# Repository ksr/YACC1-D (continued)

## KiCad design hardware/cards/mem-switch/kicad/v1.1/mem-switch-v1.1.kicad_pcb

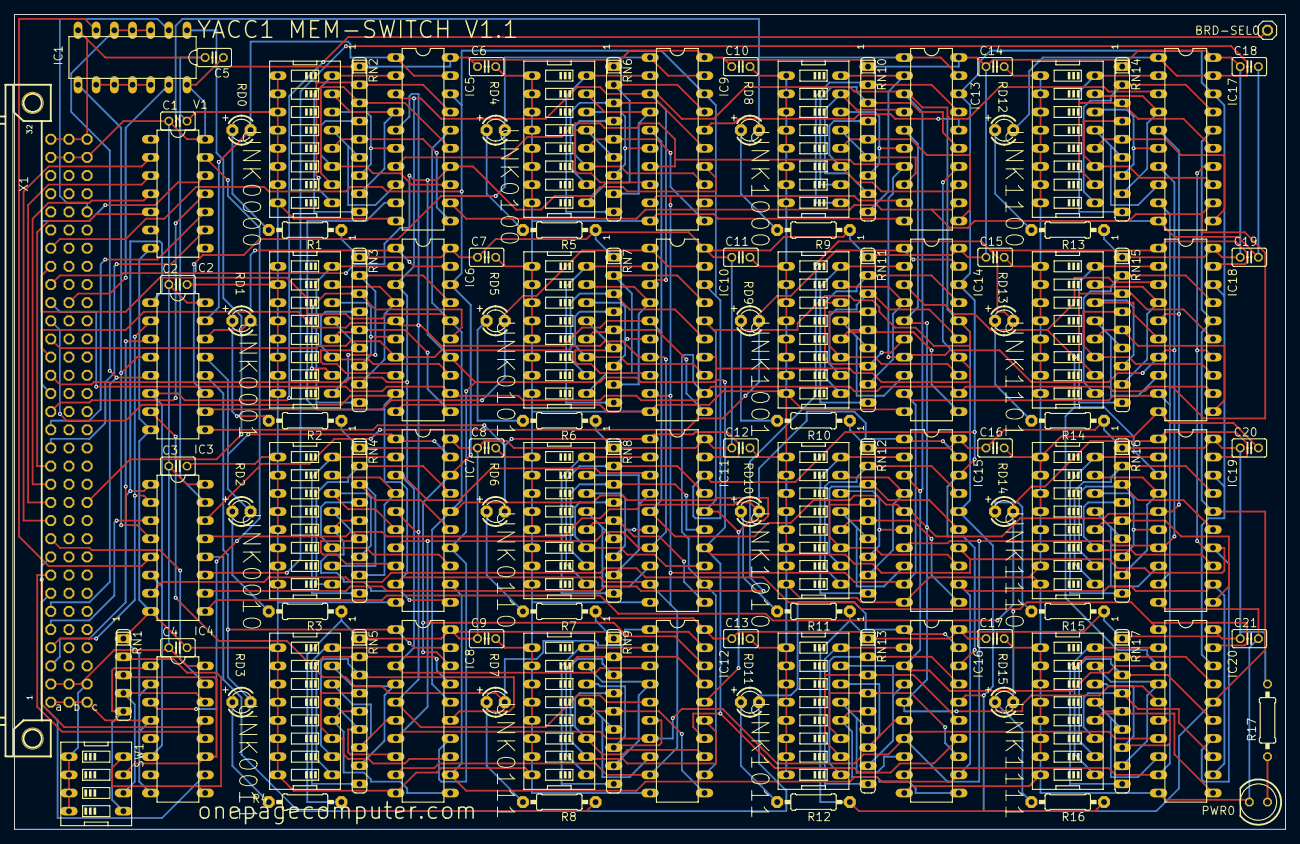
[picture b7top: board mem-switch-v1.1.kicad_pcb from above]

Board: 2 copper layers, 177.8 x 114.0 mm, 112 parts (0 on the bottom side), 199 nets.

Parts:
BRD-SEL0: PINHD-1X1; 1X01
C1, C2, C3, C4, C5, C6, C7, C8, C9, C10, C11, C12, C13, C14, C15, C16, C17, C18, C19, C20, C21: C025-025X050
IC1: 74ALS27N; DIL14
IC2, IC3: 74LS138N; DIL16
IC4: 74LS85N; DIL16
IC5, IC6, IC7, IC8, IC9, IC10, IC11, IC12, IC13, IC14, IC15, IC16, IC17, IC18, IC19, IC20: 74LS244N; DIL20
PWR0: LED5MM
R1, R2, R3, R4, R5, R6, R7, R8, R9, R10, R11, R12, R13, R14, R15, R16: 0207_10
R17: 330; 0207_10
RD0, RD1, RD2, RD3, RD4, RD5, RD6, RD7, RD8, RD9, RD10, RD11, RD12, RD13, RD14, RD15: LED3MM
RN1: SIL5
RN2, RN3, RN4, RN5, RN6, RN7, RN8, RN9, RN10, RN11, RN12, RN13, RN14, RN15, RN16, RN17: SIL9
SW1: EDG-04
UNK0000, UNK0001, UNK0010, UNK0011, UNK0100, UNK0101, UNK0110, UNK0111, UNK1000, UNK1001, UNK1010, UNK1011, UNK1100, UNK1101, UNK1110, UNK1111: EDG-08
V1: 744078N; DIL14
X1: FABC96R

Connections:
-BUS-EN: IC1.2, X1.C28
-MEM-RD: IC1.13, X1.B23
-VMA: IC1.1, X1.C12
ADDR0: IC2.1, IC3.1, X1.A3
ADDR1: IC2.2, IC3.2, X1.A4
ADDR2: IC2.3, IC3.3, X1.A5
ADDR3: IC1.3, IC1.4, IC1.5, IC2.5, X1.A6
ADDR4: IC4.10, X1.A7
ADDR5: IC4.12, X1.A8
ADDR6: IC4.13, X1.A9
ADDR7: IC4.15, X1.A10
ADDR8: V1.2, X1.A11
ADDR9: V1.3, X1.A12
ADDR10: V1.4, X1.A13
ADDR11: V1.5, X1.A14
ADDR12: V1.9, X1.A15
ADDR13: V1.10, X1.A16
ADDR14: V1.11, X1.A17
ADDR15: V1.12, X1.A18
DATA0: IC5.3, IC6.3, IC7.3, IC8.3, IC9.3, IC10.3, IC11.3, IC12.3, IC13.3, IC14.3, IC15.3, IC16.3, IC17.3, IC18.3, IC19.3, IC20.3, X1.A19
DATA1: IC5.5, IC6.5, IC7.5, IC8.5, IC9.5, IC10.5, IC11.5, IC12.5, IC13.5, IC14.5, IC15.5, IC16.5, IC17.5, IC18.5, IC19.5, IC20.5, X1.A20
DATA2: IC5.7, IC6.7, IC7.7, IC8.7, IC9.7, IC10.7, IC11.7, IC12.7, IC13.7, IC14.7, IC15.7, IC16.7, IC17.7, IC18.7, IC19.7, IC20.7, X1.A21
DATA3: IC5.9, IC6.9, IC7.9, IC8.9, IC9.9, IC10.9, IC11.9, IC12.9, IC13.9, IC14.9, IC15.9, IC16.9, IC17.9, IC18.9, IC19.9, IC20.9, X1.A22
DATA4: IC5.12, IC6.12, IC7.12, IC8.12, IC9.12, IC10.12, IC11.12, IC12.12, IC13.12, IC14.12, IC15.12, IC16.12, IC17.12, IC18.12, IC19.12, IC20.12, X1.A23
DATA5: IC5.14, IC6.14, IC7.14, IC8.14, IC9.14, IC10.14, IC11.14, IC12.14, IC13.14, IC14.14, IC15.14, IC16.14, IC17.14, IC18.14, IC19.14, IC20.14, X1.A24
DATA6: IC5.16, IC6.16, IC7.16, IC8.16, IC9.16, IC10.16, IC11.16, IC12.16, IC13.16, IC14.16, IC15.16, IC16.16, IC17.16, IC18.16, IC19.16, IC20.16, X1.A25
DATA7: IC5.18, IC6.18, IC7.18, IC8.18, IC9.18, IC10.18, IC11.18, IC12.18, IC13.18, IC14.18, IC15.18, IC16.18, IC17.18, IC18.18, IC19.18, IC20.18, X1.A26
GND: C1.2, C2.2, C3.2, C4.2, C5.2, C6.2, C7.2, C8.2, C9.2, C10.2, C11.2, C12.2, C13.2, C14.2, C15.2, C16.2, C17.2, C18.2, C19.2, C20.2, C21.2, IC1.7, IC2.8, IC3.8, IC4.2, IC4.4, IC4.8, IC5.10, IC6.10, IC7.10, IC8.10, IC9.10, IC10.10, IC11.10, IC12.10, IC13.10, IC14.10, IC15.10, IC16.10, IC17.10, IC18.10, IC19.10, IC20.10, PWR0.K, RN1.1, UNK0000.9, UNK0000.10, UNK0000.11, UNK0000.12, UNK0000.13, UNK0000.14, UNK0000.15, UNK0000.16, UNK0001.9, UNK0001.10, UNK0001.11, UNK0001.12, UNK0001.13, UNK0001.14, UNK0001.15, UNK0001.16, UNK0010.9, UNK0010.10, UNK0010.11, UNK0010.12, UNK0010.13, UNK0010.14, UNK0010.15, UNK0010.16, UNK0011.9, UNK0011.10, UNK0011.11, UNK0011.12, UNK0011.13, UNK0011.14, UNK0011.15, UNK0011.16, UNK0100.9, UNK0100.10, UNK0100.11, UNK0100.12, UNK0100.13, UNK0100.14, UNK0100.15, UNK0100.16, UNK0101.9, UNK0101.10, UNK0101.11, UNK0101.12, UNK0101.13, UNK0101.14, UNK0101.15, UNK0101.16, UNK0110.9, UNK0110.10, UNK0110.11, UNK0110.12, UNK0110.13, UNK0110.14, UNK0110.15, UNK0110.16, UNK0111.9, UNK0111.10, UNK0111.11, UNK0111.12, UNK0111.13, UNK0111.14, UNK0111.15, UNK0111.16, UNK1000.9, UNK1000.10, UNK1000.11, UNK1000.12, UNK1000.13, UNK1000.14, UNK1000.15, UNK1000.16, UNK1001.9, UNK1001.10, UNK1001.11, UNK1001.12, UNK1001.13, UNK1001.14, UNK1001.15, UNK1001.16, UNK1010.9, UNK1010.10, UNK1010.11, UNK1010.12, UNK1010.13, UNK1010.14, UNK1010.15, UNK1010.16, UNK1011.9, UNK1011.10, UNK1011.11, UNK1011.12, UNK1011.13, UNK1011.14, UNK1011.15, UNK1011.16, UNK1100.9, UNK1100.10, UNK1100.11, UNK1100.12, UNK1100.13, UNK1100.14, UNK1100.15, UNK1100.16, UNK1101.9, UNK1101.10, UNK1101.11, UNK1101.12, UNK1101.13, UNK1101.14, UNK1101.15, UNK1101.16, UNK1110.9, UNK1110.10, UNK1110.11, UNK1110.12, UNK1110.13, UNK1110.14, UNK1110.15, UNK1110.16, UNK1111.9, UNK1111.10, UNK1111.11, UNK1111.12, UNK1111.13, UNK1111.14, UNK1111.15, UNK1111.16, V1.7, X1.A1, X1.A32, X1.B1, X1.B32, X1.C1, X1.C32
unnamed: IC5.17, RN2.2, UNK0000.1
unnamed: IC5.15, RN2.3, UNK0000.2
unnamed: IC5.13, RN2.4, UNK0000.3
unnamed: IC5.11, RN2.5, UNK0000.4
unnamed: IC5.8, RN2.6, UNK0000.5
unnamed: BRD-SEL0.1, IC2.6, IC3.6, IC4.6
unnamed: IC5.6, RN2.7, UNK0000.6
unnamed: IC5.4, RN2.8, UNK0000.7
unnamed: IC5.2, RN2.9, UNK0000.8
unnamed: IC6.17, RN3.2, UNK0001.1
unnamed: PWR0.A, R17.1
unnamed: IC6.15, RN3.3, UNK0001.2
unnamed: IC6.13, RN3.4, UNK0001.3
unnamed: IC6.11, RN3.5, UNK0001.4
unnamed: IC6.8, RN3.6, UNK0001.5
unnamed: IC6.6, RN3.7, UNK0001.6
unnamed: IC6.4, RN3.8, UNK0001.7
unnamed: IC6.2, RN3.9, UNK0001.8
unnamed: IC1.9, IC1.10, IC1.11, IC1.12
unnamed: IC7.17, RN4.2, UNK0010.1
unnamed: IC7.15, RN4.3, UNK0010.2
unnamed: IC7.13, RN4.4, UNK0010.3
unnamed: IC7.11, RN4.5, UNK0010.4
unnamed: IC7.8, RN4.6, UNK0010.5
unnamed: IC7.6, RN4.7, UNK0010.6
unnamed: IC7.4, RN4.8, UNK0010.7
unnamed: IC7.2, RN4.9, UNK0010.8
unnamed: IC4.9, RN1.2, SW1.8
unnamed: IC8.17, RN5.2, UNK0011.1
unnamed: IC8.15, RN5.3, UNK0011.2
unnamed: IC8.13, RN5.4, UNK0011.3
unnamed: IC8.11, RN5.5, UNK0011.4
unnamed: IC8.8, RN5.6, UNK0011.5
unnamed: IC8.6, RN5.7, UNK0011.6
unnamed: IC8.4, RN5.8, UNK0011.7
unnamed: IC8.2, RN5.9, UNK0011.8
unnamed: IC1.6, IC3.5
unnamed: IC9.17, RN6.2, UNK0100.1
unnamed: IC9.15, RN6.3, UNK0100.2
unnamed: IC9.13, RN6.4, UNK0100.3
unnamed: IC9.11, RN6.5, UNK0100.4
unnamed: IC9.8, RN6.6, UNK0100.5
unnamed: IC9.6, RN6.7, UNK0100.6
unnamed: IC9.4, RN6.8, UNK0100.7
unnamed: IC9.2, RN6.9, UNK0100.8
unnamed: IC4.11, RN1.3, SW1.7
unnamed: IC10.17, RN7.2, UNK0101.1
unnamed: IC10.15, RN7.3, UNK0101.2
unnamed: IC10.13, RN7.4, UNK0101.3
unnamed: IC10.11, RN7.5, UNK0101.4
unnamed: IC10.8, RN7.6, UNK0101.5
unnamed: IC10.6, RN7.7, UNK0101.6
unnamed: IC10.4, RN7.8, UNK0101.7
unnamed: IC10.2, RN7.9, UNK0101.8
unnamed: IC4.3, V1.13
unnamed: IC11.17, RN8.2, UNK0110.1
unnamed: IC11.15, RN8.3, UNK0110.2
unnamed: IC11.13, RN8.4, UNK0110.3
unnamed: IC11.11, RN8.5, UNK0110.4
unnamed: IC11.8, RN8.6, UNK0110.5
unnamed: IC11.6, RN8.7, UNK0110.6
unnamed: IC11.4, RN8.8, UNK0110.7
unnamed: IC11.2, RN8.9, UNK0110.8
unnamed: IC4.14, RN1.4, SW1.6
unnamed: IC12.17, RN9.2, UNK0111.1
unnamed: IC12.15, RN9.3, UNK0111.2
unnamed: IC12.13, RN9.4, UNK0111.3
unnamed: IC12.11, RN9.5, UNK0111.4
unnamed: IC12.8, RN9.6, UNK0111.5
unnamed: IC12.6, RN9.7, UNK0111.6
unnamed: IC12.4, RN9.8, UNK0111.7
unnamed: IC12.2, RN9.9, UNK0111.8
unnamed: IC4.1, RN1.5, SW1.5
unnamed: IC13.17, RN10.2, UNK1000.1
unnamed: IC13.15, RN10.3, UNK1000.2
unnamed: IC13.13, RN10.4, UNK1000.3
unnamed: IC13.11, RN10.5, UNK1000.4
unnamed: IC13.8, RN10.6, UNK1000.5
unnamed: IC13.6, RN10.7, UNK1000.6
unnamed: IC13.4, RN10.8, UNK1000.7
unnamed: IC13.2, RN10.9, UNK1000.8
unnamed: IC1.8, IC2.4, IC3.4
unnamed: IC14.17, RN11.2, UNK1001.1
unnamed: IC14.15, RN11.3, UNK1001.2
unnamed: IC14.13, RN11.4, UNK1001.3
unnamed: IC14.11, RN11.5, UNK1001.4
unnamed: IC14.8, RN11.6, UNK1001.5
unnamed: IC14.6, RN11.7, UNK1001.6
unnamed: IC14.4, RN11.8, UNK1001.7
unnamed: IC14.2, RN11.9, UNK1001.8
unnamed: R1.2, RD0.A
unnamed: IC15.17, RN12.2, UNK1010.1
unnamed: IC15.15, RN12.3, UNK1010.2
unnamed: IC15.13, RN12.4, UNK1010.3
unnamed: IC15.11, RN12.5, UNK1010.4
unnamed: IC15.8, RN12.6, UNK1010.5
unnamed: IC15.6, RN12.7, UNK1010.6
unnamed: IC15.4, RN12.8, UNK1010.7
unnamed: IC15.2, RN12.9, UNK1010.8
unnamed: R2.2, RD1.A
unnamed: IC16.17, RN13.2, UNK1011.1
unnamed: IC16.15, RN13.3, UNK1011.2
unnamed: IC16.13, RN13.4, UNK1011.3
unnamed: IC16.11, RN13.5, UNK1011.4
unnamed: IC16.8, RN13.6, UNK1011.5
unnamed: IC16.6, RN13.7, UNK1011.6
unnamed: IC16.4, RN13.8, UNK1011.7
unnamed: IC16.2, RN13.9, UNK1011.8
unnamed: R3.2, RD2.A
unnamed: IC17.17, RN14.2, UNK1100.1
unnamed: IC17.15, RN14.3, UNK1100.2
unnamed: IC17.13, RN14.4, UNK1100.3
unnamed: IC17.11, RN14.5, UNK1100.4
unnamed: IC17.8, RN14.6, UNK1100.5
unnamed: IC17.6, RN14.7, UNK1100.6
unnamed: IC17.4, RN14.8, UNK1100.7
unnamed: IC17.2, RN14.9, UNK1100.8
unnamed: R4.2, RD3.A
unnamed: IC18.17, RN15.2, UNK1101.1
unnamed: IC18.15, RN15.3, UNK1101.2
unnamed: IC18.13, RN15.4, UNK1101.3
unnamed: IC18.11, RN15.5, UNK1101.4
unnamed: IC18.8, RN15.6, UNK1101.5
unnamed: IC18.6, RN15.7, UNK1101.6
unnamed: IC18.4, RN15.8, UNK1101.7
unnamed: IC18.2, RN15.9, UNK1101.8
unnamed: R5.2, RD4.A
unnamed: IC19.17, RN16.2, UNK1110.1
unnamed: IC19.15, RN16.3, UNK1110.2
unnamed: IC19.13, RN16.4, UNK1110.3
unnamed: IC19.11, RN16.5, UNK1110.4
unnamed: IC19.8, RN16.6, UNK1110.5
unnamed: IC19.6, RN16.7, UNK1110.6
unnamed: IC19.4, RN16.8, UNK1110.7
unnamed: IC19.2, RN16.9, UNK1110.8
unnamed: R6.2, RD5.A
unnamed: IC20.17, RN17.2, UNK1111.1
unnamed: IC20.15, RN17.3, UNK1111.2
unnamed: IC20.13, RN17.4, UNK1111.3
unnamed: IC20.11, RN17.5, UNK1111.4
unnamed: IC20.8, RN17.6, UNK1111.5
unnamed: IC20.6, RN17.7, UNK1111.6
unnamed: IC20.4, RN17.8, UNK1111.7
unnamed: IC20.2, RN17.9, UNK1111.8
unnamed: R7.2, RD6.A
unnamed: R8.2, RD7.A
unnamed: R9.2, RD8.A
unnamed: R10.2, RD9.A
unnamed: R11.2, RD10.A
unnamed: R12.2, RD11.A
unnamed: R13.2, RD12.A
unnamed: R14.2, RD13.A
unnamed: R15.2, RD14.A
unnamed: R16.2, RD15.A
SW0: IC2.15, IC5.1, IC5.19, RD0.K
SW1: IC2.14, IC6.1, IC6.19, RD1.K
SW2: IC2.13, IC7.1, IC7.19, RD2.K
SW3: IC2.12, IC8.1, IC8.19, RD3.K
SW4: IC2.11, IC9.1, IC9.19, RD4.K
SW5: IC2.10, IC10.1, IC10.19, RD5.K
SW6: IC2.9, IC11.1, IC11.19, RD6.K
SW7: IC2.7, IC12.1, IC12.19, RD7.K
SW8: IC3.15, IC13.1, IC13.19, RD8.K
SW9: IC3.14, IC14.1, IC14.19, RD9.K
SW10: IC3.13, IC15.1, IC15.19, RD10.K
SW11: IC3.12, IC16.1, IC16.19, RD11.K
SW12: IC3.11, IC17.1, IC17.19, RD12.K
SW13: IC3.10, IC18.1, IC18.19, RD13.K
SW14: IC3.9, IC19.1, IC19.19, RD14.K
SW15: IC3.7, IC20.1, IC20.19, RD15.K
VCC: C1.1, C2.1, C3.1, C4.1, C5.1, C6.1, C7.1, C8.1, C9.1, C10.1, C11.1, C12.1, C13.1, C14.1, C15.1, C16.1, C17.1, C18.1, C19.1, C20.1, C21.1, IC1.14, IC2.16, IC3.16, IC4.16, IC5.20, IC6.20, IC7.20, IC8.20, IC9.20, IC10.20, IC11.20, IC12.20, IC13.20, IC14.20, IC15.20, IC16.20, IC17.20, IC18.20, IC19.20, IC20.20, R1.1, R2.1, R3.1, R4.1, R5.1, R6.1, R7.1, R8.1, R9.1, R10.1, R11.1, R12.1, R13.1, R14.1, R15.1, R16.1, R17.2, RN2.1, RN3.1, RN4.1, RN5.1, RN6.1, RN7.1, RN8.1, RN9.1, RN10.1, RN11.1, RN12.1, RN13.1, RN14.1, RN15.1, RN16.1, RN17.1, SW1.1, SW1.2, SW1.3, SW1.4, V1.14, X1.A2, X1.A31, X1.B2, X1.B31, X1.C2, X1.C31

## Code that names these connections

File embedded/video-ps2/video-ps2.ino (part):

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   video-ps2 (2026-10-22) - the PS/2 keyboard and mouse controller of the YACC1 video card V4.0
   (hardware/cards/video/kicad/v4.0, embedded/video-ps2/README.md; the PS/2 section is the never-built V2.0 design's).
   Revised 2026-10-22 after the V2.0 design's review: BUSY and SRC swapped (V2-1,
   Optiboot's LED pin PB5 is now the SRC output), host-to-device bit count (V2-3), LDDATA idle high (V2-7), MD released
   with pull-ups (V2-9), the V2-18 robustness items. 2026-10-23 after the re-review (R2-10): ps2_wait() takes only reply bytes; a key typed while a command waits for its answer goes to the key queue.

   An ATmega328P at 16 MHz between two PS/2 jacks and the YACC1 bus. The CPU never talks to it directly: it reads and
   writes three latches on the card (so a 1 MHz CPU never waits for this firmware):
     IN PE   a 74LS374 the firmware loads (MD0..7 + LDDATA); loading it sets FULL, the CPU's read clears FULL
     IN PD   status (a 74LS244): bit 0 FULL, bit 1 SRC (this pin: 0 keyboard, 1 mouse), bit 2 BUSY
     OUT PD  a 74LS374 the CPU loads (sets BUSY); the firmware reads it onto MD0..7 with -RDCMD, which clears BUSY

   Pins (Arduino Uno numbering = the ATmega328P's port pins):
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     D3        PD3 INT1              mouse CLOCK (J3 pin 5)
     D4        PD4                   keyboard DATA (J2 pin 1)
     D5        PD5                   mouse DATA (J3 pin 1)
     D6        PD6  LDDATA  out      idle high (10k pull-up R22); a low pulse: the data latch takes MD0..7 and FULL
                                     sets on its rising edge
     D7        PD7  -RDCMD  out      low: the command latch drives MD0..7 (and BUSY clears); 10k pull-up R23
     A0..A5    PC0..PC5  MD0..MD5    the local bus (both directions)
     D8, D9    PB0, PB1  MD6, MD7
     D10       PB2  FULL    in       1 = the CPU has not read the last byte yet
     D11       PB3  BUSY    in       1 = the CPU wrote a command (OUT PD) the firmware has not read yet
     D12       PB4  INTREQ  out      1 = request -INT: the card ANDs it with FULL (IC54/B) into IC27/D (open
                                     collector) and jumper JP3 INT-EN; 10k pull-down R24
     D13       PB5  SRC     out      0 = the byte in the data latch is from the keyboard, 1 = from the mouse
                                     (PB5 is the Uno bootloader's LED pin: it may flash during Optiboot, harmless on
                                     SRC, which only matters with FULL)
   The PS/2 lines are open drain: a pin is either an input (the 4.7k pull-up makes 1) or an output driving 0.
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   whole (a packet is queued only when all three bytes are in).
*/

#define KCLK 2
#define MCLK 3
#define KDAT 4
#define MDAT 5
#define LDDATA 6
#define RDCMD 7
#define PIN_FULL 10
#define PIN_BUSY 11                    // V2-1: BUSY on PB3, SRC on PB5 (Optiboot's LED pin)
#define PIN_INTREQ 12
#define PIN_SRC 13

#define QSIZE 64                      // the queue to the CPU: (byte, source) pairs
#define RXSIZE 64                     // each port's receive ring (64: the mouse's packets during LED commands)
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}

void feed_cpu() {                                 // the next queued byte into the data latch once the CPU took the last
  if (qh == qt || digitalRead(PIN_FULL)) return;
  delayMicroseconds(5);                           // FULL is held clear while the CPU's read strobe lasts: INP holds
  if (digitalRead(PIN_FULL)) return;              // -IO-RD 7 clocks (7 us at 1 MHz); a load inside it is caught below
  digitalWrite(PIN_SRC, qsrc[qt]);
  md_write(qbyte[qt]);
  delayMicroseconds(1);
  digitalWrite(LDDATA, LOW);                      // LDDATA idles high (V2-7): a low pulse,
  delayMicroseconds(1);
  digitalWrite(LDDATA, HIGH);                     // the 74LS374 and FULL take the byte on its rising edge
  md_release();
  if (digitalRead(PIN_FULL)) qt = (qt + 1) % QSIZE;   // else a read strobe overlapped: load it again next time
}

// ---------------------------------------------------------------- keyboard: set-2 scan codes -> ASCII
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
void setup() {
  Serial.begin(38400);
  pinMode(KCLK, INPUT); pinMode(KDAT, INPUT); pinMode(MCLK, INPUT); pinMode(MDAT, INPUT);   // released: the pull-ups
  digitalWrite(LDDATA, HIGH); pinMode(LDDATA, OUTPUT);     // idle high, as the pull-up held it through the reset
  digitalWrite(RDCMD, HIGH); pinMode(RDCMD, OUTPUT);
  pinMode(PIN_FULL, INPUT); pinMode(PIN_BUSY, INPUT);
  pinMode(PIN_SRC, OUTPUT); pinMode(PIN_INTREQ, OUTPUT); digitalWrite(PIN_INTREQ, LOW);
  md_release();
  attachInterrupt(digitalPinToInterrupt(KCLK), kb_isr, FALLING);
  attachInterrupt(digitalPinToInterrupt(MCLK), ms_isr, FALLING);
  Serial.println(F("video-ps2 2026-10-23"));
  if (digitalRead(PIN_BUSY)) read_command();      // a command latched before a reset: dropped
  start_all();
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  while ((b = ps2_next(ms)) >= 0) mouse_byte(b);
  if (digitalRead(PIN_BUSY)) command(read_command());
  feed_cpu();
  digitalWrite(PIN_INTREQ, int_on && !acked && digitalRead(PIN_FULL));
}

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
